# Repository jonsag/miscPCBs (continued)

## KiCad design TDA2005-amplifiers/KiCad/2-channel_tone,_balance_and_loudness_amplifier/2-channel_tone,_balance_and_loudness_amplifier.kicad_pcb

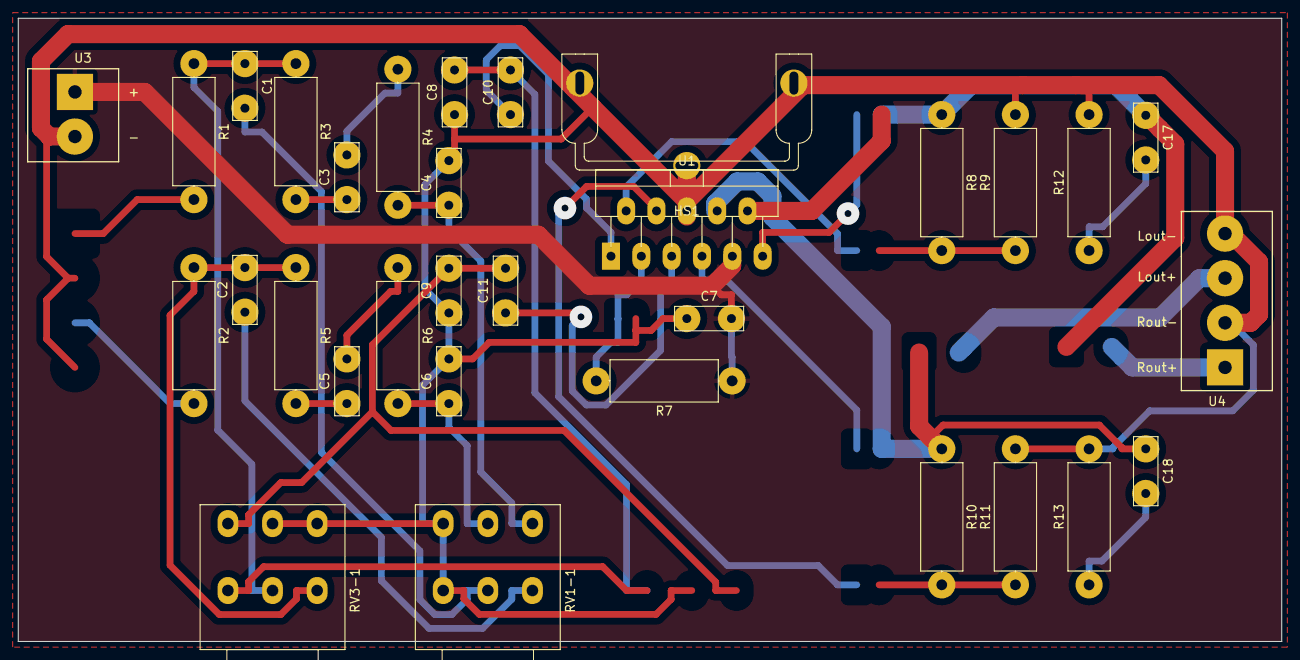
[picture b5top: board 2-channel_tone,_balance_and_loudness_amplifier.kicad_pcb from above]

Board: 2 copper layers, 141.6 x 69.8 mm, 32 parts (0 on the bottom side), 23 nets.

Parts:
C1, C2: 47n; C_Disc_D7.5mm_W2.5mm_P5.00mm_larger
C3, C5, C8, C9: 2.2n; C_Disc_D7.5mm_W2.5mm_P5.00mm_larger
C4, C6: 150n; C_Disc_D7.5mm_W2.5mm_P5.00mm_larger
C7, C17, C18: 100n; C_Disc_D7.5mm_W2.5mm_P5.00mm_larger
C10, C11: 220n; C_Disc_D7.5mm_W2.5mm_P5.00mm_larger
HS1: Heatsink_Pad; EK-41002859
R1, R2: 5.6k; R_Axial_DIN0414_L11.9mm_D4.5mm_P15.24mm_Horizontal_larger
R3, R5: 47k; R_Axial_DIN0414_L11.9mm_D4.5mm_P15.24mm_Horizontal_larger
R4, R6: 2.7k; R_Axial_DIN0414_L11.9mm_D4.5mm_P15.24mm_Horizontal_larger
R7: 120k; R_Axial_DIN0414_L11.9mm_D4.5mm_P15.24mm_Horizontal_larger
R8, R10: 100k; R_Axial_DIN0414_L11.9mm_D4.5mm_P15.24mm_Horizontal_larger
R9, R11: 3.3R; R_Axial_DIN0414_L11.9mm_D4.5mm_P15.24mm_Horizontal_larger
R12, R13: 1R; R_Axial_DIN0414_L11.9mm_D4.5mm_P15.24mm_Horizontal_larger
RV1-1, RV3-1: Dual_potentiometer; Potentiometer_Piher_PC-16_Dual_Horizontal_larger
U1: TDA2005; TO-220-11_P3.4x5.08mm_StaggerOdd_Lead4.85mm_Vertical_large
U3: 2-pole_power_in_screw_terminal
U4: 4-pole_RL-output_screw_terminal; 4-pole_screw_terminal_RL_output

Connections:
+15V: C7.2, R7.1, U1.9 (V+), U3.1 (+)
GND: C4.2, C6.2, C7.1, C8.1, C9.1, HS1.1, R9.2, R11.2, R12.2, R13.2, RV1-1.1 (2), RV1-1.4 (5), RV3-1.5 (6), RV3-1.6 (3), U1.6 (GND), U3.2 (-), U4.2 (Rout-), U4.4 (Lout-)
unnamed: C3.1, R3.2
unnamed: C3.2, R4.1
unnamed: C5.1, R5.2
unnamed: C5.2, R6.1
unnamed: C17.1, R8.1, U1.10
unnamed: C18.1, R10.1, U1.8
unnamed: R8.2, R9.1
unnamed: R10.2, R11.1
unnamed: C17.2, R12.1
unnamed: C18.2, R13.1
unnamed: C1.2, RV1-1.2 (1)
unnamed: C4.1, R4.2, RV1-1.6 (3)
unnamed: C2.1, RV1-1.3 (4)
unnamed: C6.1, R6.2, RV1-1.5 (6)
unnamed: C1.1, R1.1, R3.1, RV3-1.2 (1)
unnamed: C8.2, C10.2, RV3-1.1 (2)
unnamed: C2.2, R2.1, R5.1, RV3-1.3 (4)
unnamed: C9.2, C11.2, RV3-1.4 (5)
unnamed: C10.1, U1.1 (+)
unnamed: R7.2, U1.3 (SVRR)
unnamed: C11.1, U1.5 (+)

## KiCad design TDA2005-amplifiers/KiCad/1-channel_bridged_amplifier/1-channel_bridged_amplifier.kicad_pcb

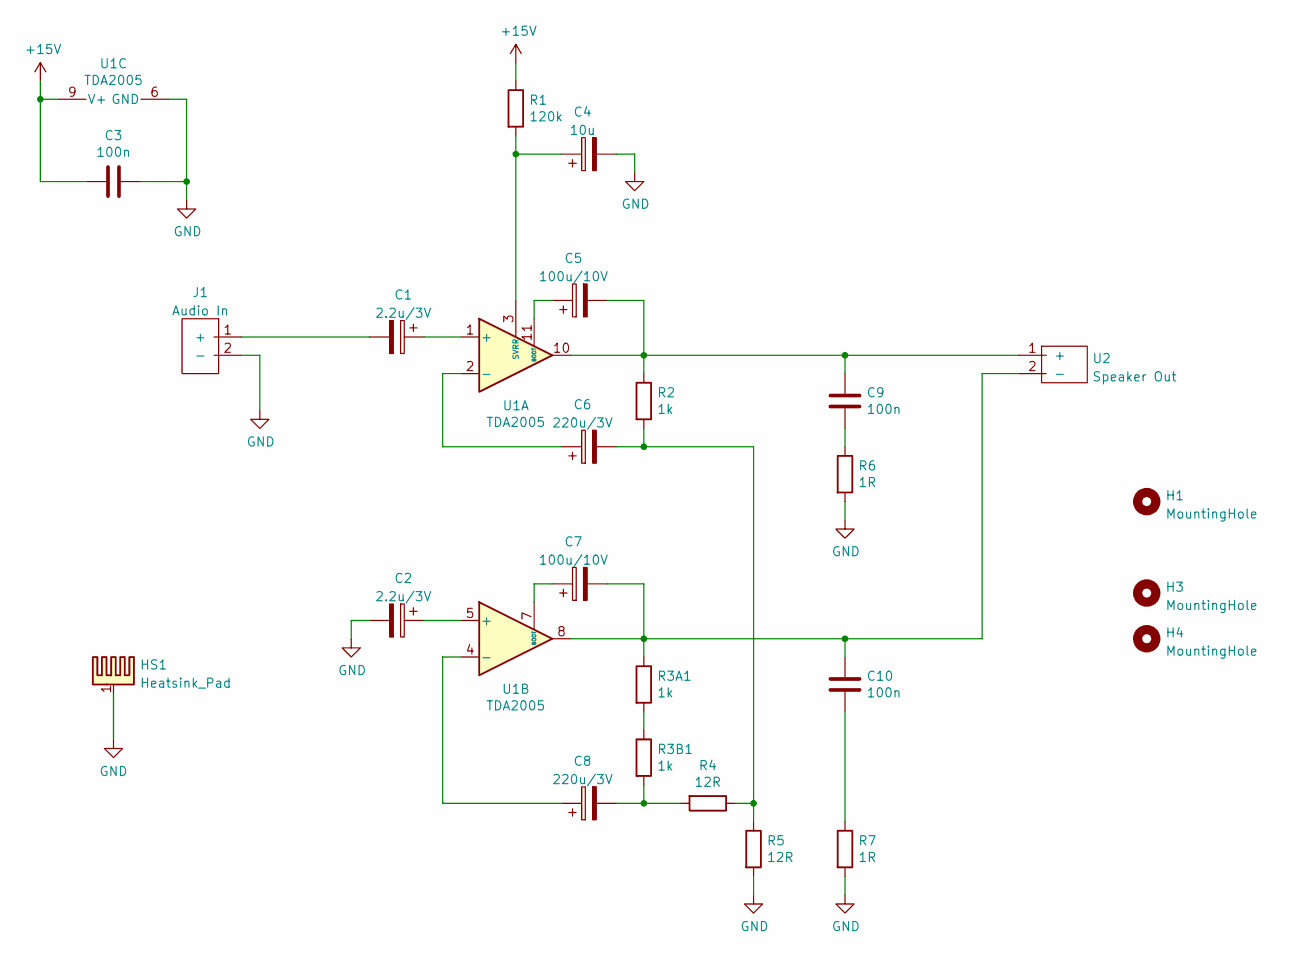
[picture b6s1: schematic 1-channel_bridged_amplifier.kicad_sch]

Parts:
C1, C2: 2.2u/3V; CP_Radial_D5.0mm_P2.00mm_larger
C3, C9, C10: 100n; C_Disc_D7.5mm_W2.5mm_P5.00mm_larger
C4: 10u; CP_Radial_D5.0mm_P2.00mm_larger
C5, C7: 100u/10V; CP_Radial_D8.0mm_P3.50mm_large
C6, C8: 220u/3V; CP_Radial_D10.0mm_P5.00mm_larger
H1, H3, H4: MountingHole; MountingHole_3.2mm_M3
HS1: Heatsink_Pad; EK-41002859
J1: Audio In; 2-pin JST Audio
R1: 120k; R_Axial_DIN0414_L11.9mm_D4.5mm_P15.24mm_Horizontal_larger
R2, R3A1, R3B1: 1k; R_Axial_DIN0414_L11.9mm_D4.5mm_P15.24mm_Horizontal_larger
R4, R5: 12R; R_Axial_DIN0414_L11.9mm_D4.5mm_P15.24mm_Horizontal_larger
R6, R7: 1R; R_Axial_DIN0414_L11.9mm_D4.5mm_P15.24mm_Horizontal_larger
U1: TDA2005; TO-220-11_P3.4x5.08mm_StaggerOdd_Lead4.85mm_Vertical_large
U2: Speaker Out; 2-pole_power_in_screw_terminal

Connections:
+15V: C3.2, R1.1, U1.9 (V+)
GND: C2.2, C3.1, C4.2, HS1.1, J1.2 (-), R5.2, R6.2, R7.2, U1.6 (GND)
unnamed: C1.2, J1.1 (+)
unnamed: C5.2, C9.1, R2.1, U1.10, U2.1 (+)
unnamed: C9.2, R6.1
unnamed: C7.2, C10.1, R3A1.1, U1.8, U2.2 (-)
unnamed: C10.2, R7.1
unnamed: C4.1, R1.2, U1.3 (SVRR)
unnamed: C6.2, R2.2, R4.1, R5.1
unnamed: R3A1.2, R3B1.1
unnamed: C8.2, R3B1.2, R4.2
unnamed: C1.1, U1.1 (+)
unnamed: C6.1, U1.2 (-)
unnamed: C8.1, U1.4 (-)
unnamed: C2.1, U1.5 (+)
unnamed: C7.1, U1.7 (BOOT)
unnamed: C5.1, U1.11 (BOOT)

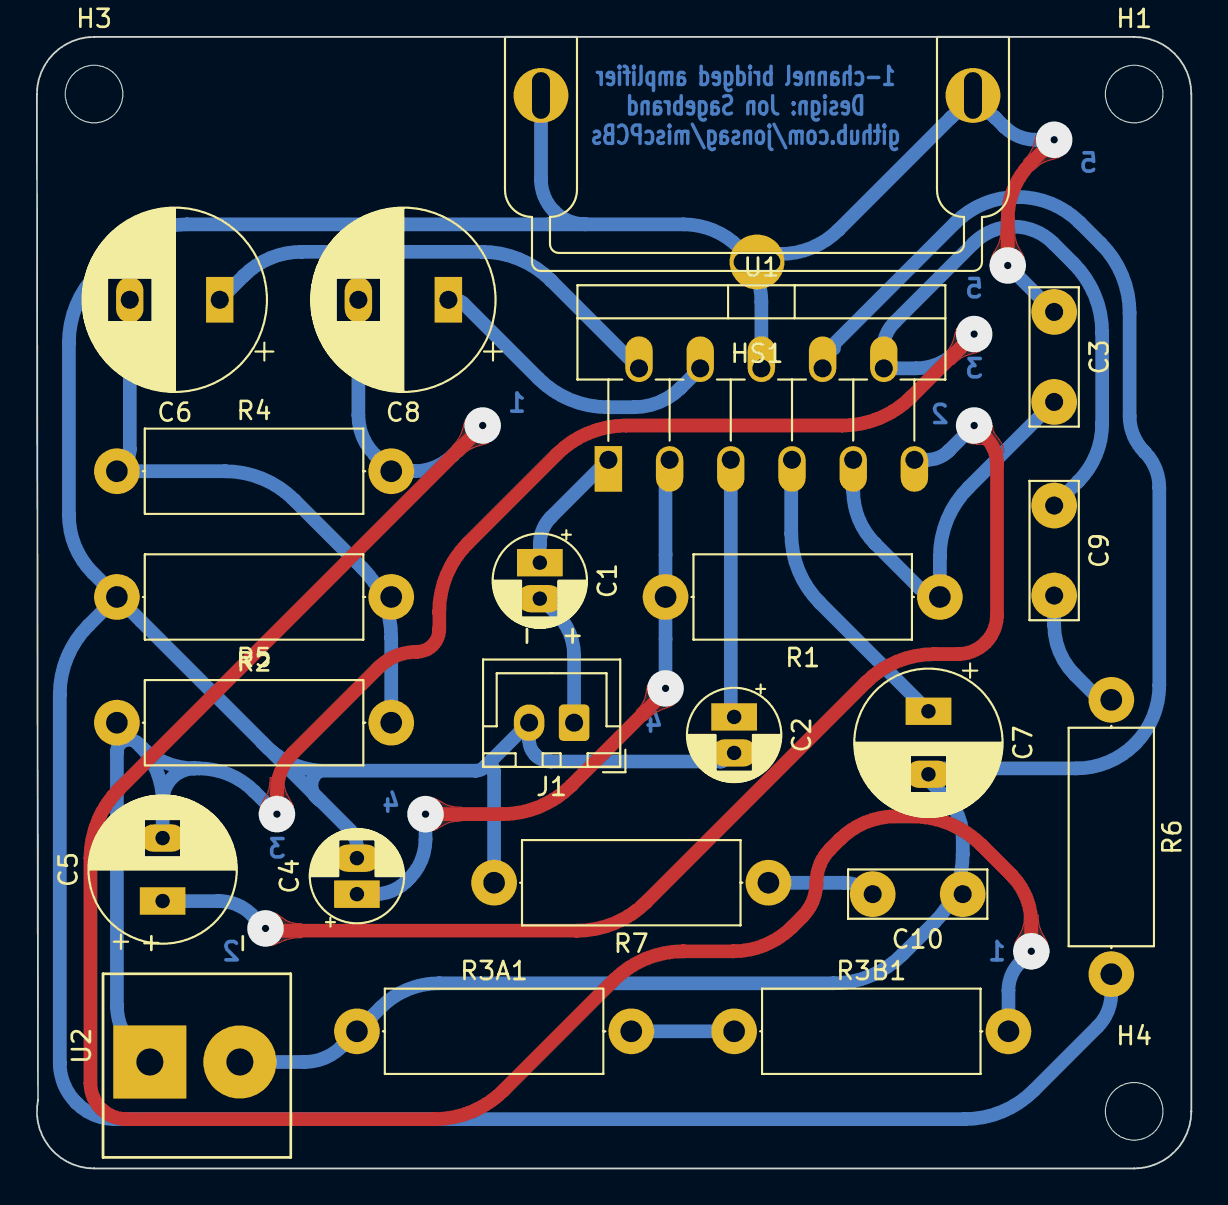
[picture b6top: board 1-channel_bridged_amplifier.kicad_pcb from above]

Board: 2 copper layers, 64.1 x 62.9 mm, 25 parts (0 on the bottom side), 17 nets.

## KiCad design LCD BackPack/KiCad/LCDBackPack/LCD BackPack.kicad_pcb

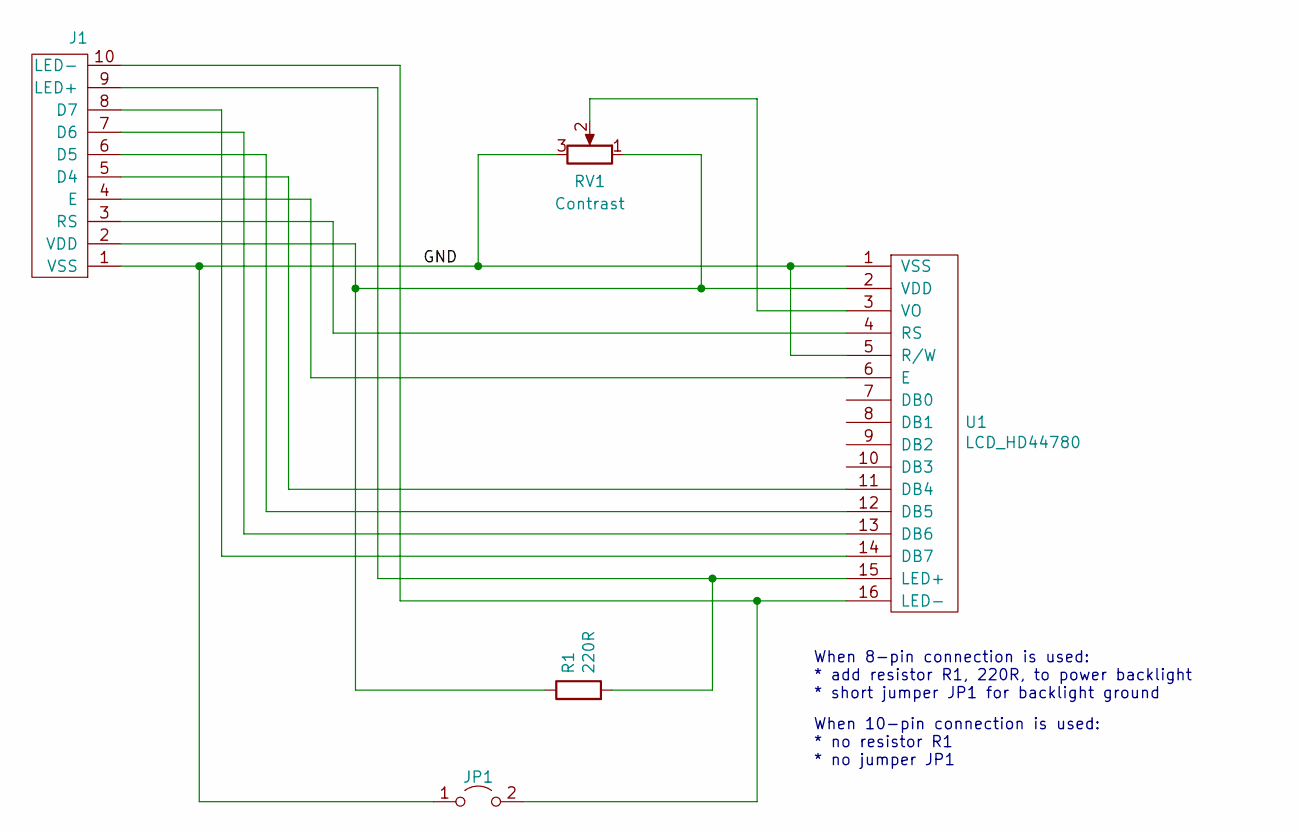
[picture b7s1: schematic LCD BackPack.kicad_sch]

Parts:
J1: 10-pin_header_LCD_interface; 10-pin_LCD_header_larger_pads
JP1: Jumper_2_Open; Angled_Jumper_1x02_P2.54mm_large
R1: 220R; R_Axial_DIN0207_L6.3mm_D2.5mm_P10.16mm_Horizontal_larger_pa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
RV1: Contrast; Potentiometer_Bourns_3339P_Vertical_large
U1: LCD_HD44780; LCD_HD44780_16x2_w_headers_no outlinelarge

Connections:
/GND: J1.1 (VSS), JP1.1 (A), RV1.3, U1.1 (VSS), U1.5 (R/W)
unnamed: J1.2 (VDD), R1.1, RV1.1, U1.2 (VDD)
unnamed: J1.3 (RS), U1.4 (RS)
unnamed: J1.4 (E), U1.6 (E)
unnamed: J1.5 (D4), U1.11 (DB4)
unnamed: J1.6 (D5), U1.12 (DB5)
unnamed: J1.7 (D6), U1.13 (DB6)
unnamed: J1.8 (D7), U1.14 (DB7)
unnamed: J1.9 (LED+), R1.2, U1.15 (LED+)
unnamed: J1.10 (LED-), JP1.2 (B), U1.16 (LED-)
unnamed: RV1.2, U1.3 (VO)

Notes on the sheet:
When 10-pin connection is used: * no resistor R1 * no jumper JP1
When 8-pin connection is used: * add resistor R1, 220R, to power backlight * short jumper JP1 for backlight ground

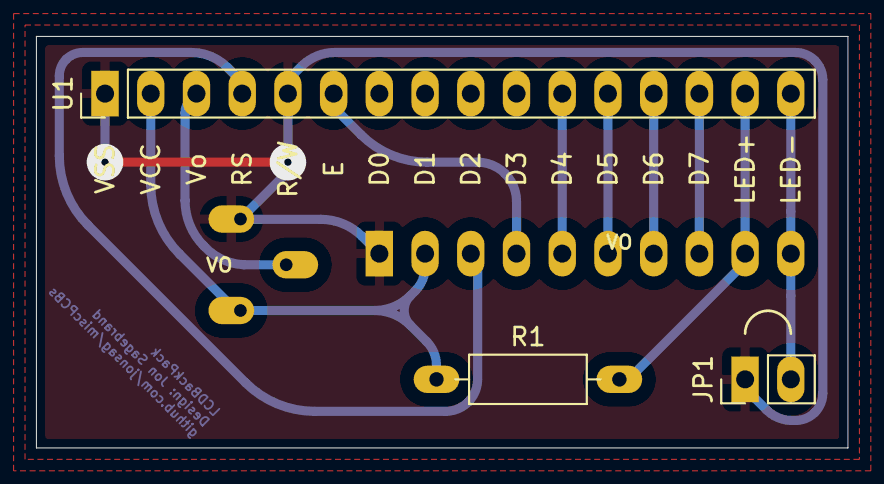
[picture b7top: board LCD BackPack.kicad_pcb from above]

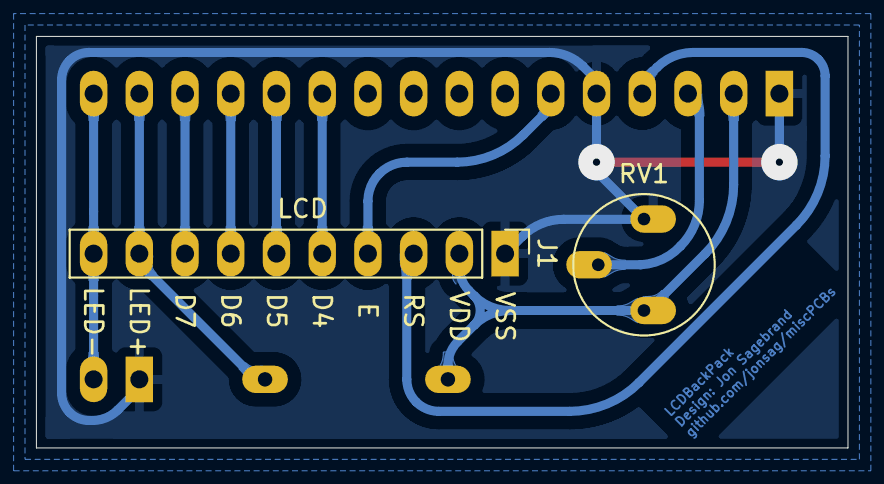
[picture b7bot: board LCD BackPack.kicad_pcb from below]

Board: 2 copper layers, 45.1 x 22.9 mm, 5 parts (2 on the bottom side), 11 nets.

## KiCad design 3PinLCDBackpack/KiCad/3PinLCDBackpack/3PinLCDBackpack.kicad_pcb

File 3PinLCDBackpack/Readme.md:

# 3PinLCDBackPack

## Links

* [https://www.instructables.com/Hookup-a-16-pin-HD44780-LCD-to-an-Arduino-in-6-sec/](https://www.instructables.com/Hookup-a-16-pin-HD44780-LCD-to-an-Arduino-in-6-sec/)'

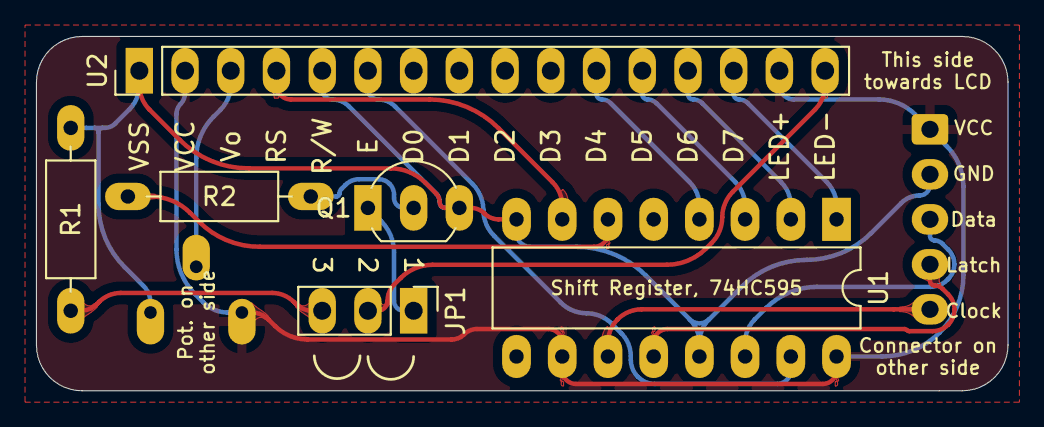
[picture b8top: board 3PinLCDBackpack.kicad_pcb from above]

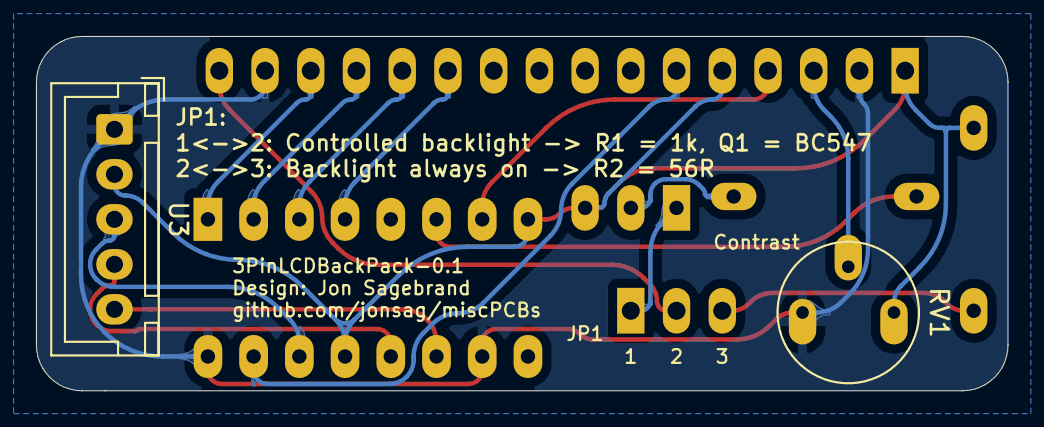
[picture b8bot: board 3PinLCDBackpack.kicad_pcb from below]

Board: 2 copper layers, 54.0 x 19.7 mm, 8 parts (2 on the bottom side), 17 nets.

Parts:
JP1: Backlight control; Angled_Jumper_1x03_P2.54mm_large
Q1: BC547; TO-92_Inline_Wide_large
R1: 56R; R_Axial_DIN0207_L6.3mm_D2.5mm_P10.16mm_Horizontal_larger_pa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
R2: 1k; R_Axial_DIN0207_L6.3mm_D2.5mm_P10.16mm_Horizontal_larger_pa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
RV1: 10k; Potentiometer_Bourns_3339P_Vertical_large
U1: 74HC595; DIP-16_W7.62mm_LongPads w socket
U2: LCD_HD44780; LCD_HD44780_16x2_w_headers_no outlinelarge
U3: 5-pin_LiquidCrystal595_connector; 5-pin JST LiquidCrystal595

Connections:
GND: Q1.3 (E), R1.1, RV1.3, U1.8 (GND), U1.13 (~OE), U2.1 (VSS), U2.5 (R/W), U3.2 (GND)
unnamed: JP1.1 (A), Q1.1 (C)
unnamed: JP1.2 (C), U2.16 (LED-)
unnamed: JP1.3 (B), R1.2
unnamed: Q1.2 (B), R2.2
unnamed: R2.1, U1.6 (QG)
unnamed: RV1.2, U2.3 (VO)
unnamed: U1.1 (QB), U2.14 (DB7)
unnamed: U1.2 (QC), U2.13 (DB6)
unnamed: U1.3 (QD), U2.12 (DB5)
unnamed: U1.4 (QE), U2.11 (DB4)
unnamed: U1.7 (QH), U2.4 (RS)
unnamed: U1.11 (SRCLK), U3.5 (Clock)
unnamed: U1.12 (RCLK), U3.4 (Latch)
unnamed: U1.14 (SER), U3.3 (Data)
unnamed: U1.15 (QA), U2.6 (E)
VCC: RV1.1, U1.10 (~SRCLR), U1.16 (VCC), U2.2 (VDD), U2.15 (LED+), U3.1 (VCC)

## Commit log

2020-02-03 added LCD BackPack
2020-02-08 added KiCad
2020-02-08 copper pour
2020-02-15 added 3 pin LCD
2020-03-07 new layout
2020-05-10 added TDA2005R amplifier
2020-05-10 larger pads
2020-05-10 wider tracks and text
2020-05-12 new component sizes
2020-05-13 new resistors, new heatsink
2020-05-17 new amplifiers
2020-05-17 new potentiometers
2021-09-27 3 pin LCD
2021-09-27 LiquidCrystal595 arduino library
2021-09-28 ESP-programmer
2021-12-27 new switches, better 3d
2022-05-17 3 pin lcd backpack, new pcb
2022-05-17 esp-01 programmer board
2022-05-17 kicad6
2022-05-18 amplifier
2022-05-18 deletions
2022-05-18 bridged amplifier
2022-05-18 2-channel
2022-05-18 3-pin
2022-06-10 3pinLCD
2022-06-11 new pcb for 3pinlcd
2022-06-11 rotary tool
2022-06-11 readded LCD backpack
2022-06-11 new sketch
2022-06-11 lcd backpack
2022-06-12 ESPxxProgrammer
2022-09-01 8-pin LCD
2022-10-23 moved to another git
2022-10-30 fm transmitter
2025-02-01 revision
2025-02-01 cleaning and revising
2025-02-02 more revisions
2025-02-03 UBER LCD Control
2025-02-06 IR receiver
2025-02-07 RPi IR
